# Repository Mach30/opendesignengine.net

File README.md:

This is a static checkout of opendesignengine.net, a web portal that was developed by [Mach 30](http://mach30.org) to make it so that open source hardware projects could post not just the plans, but the entire design process of their hardware projects.

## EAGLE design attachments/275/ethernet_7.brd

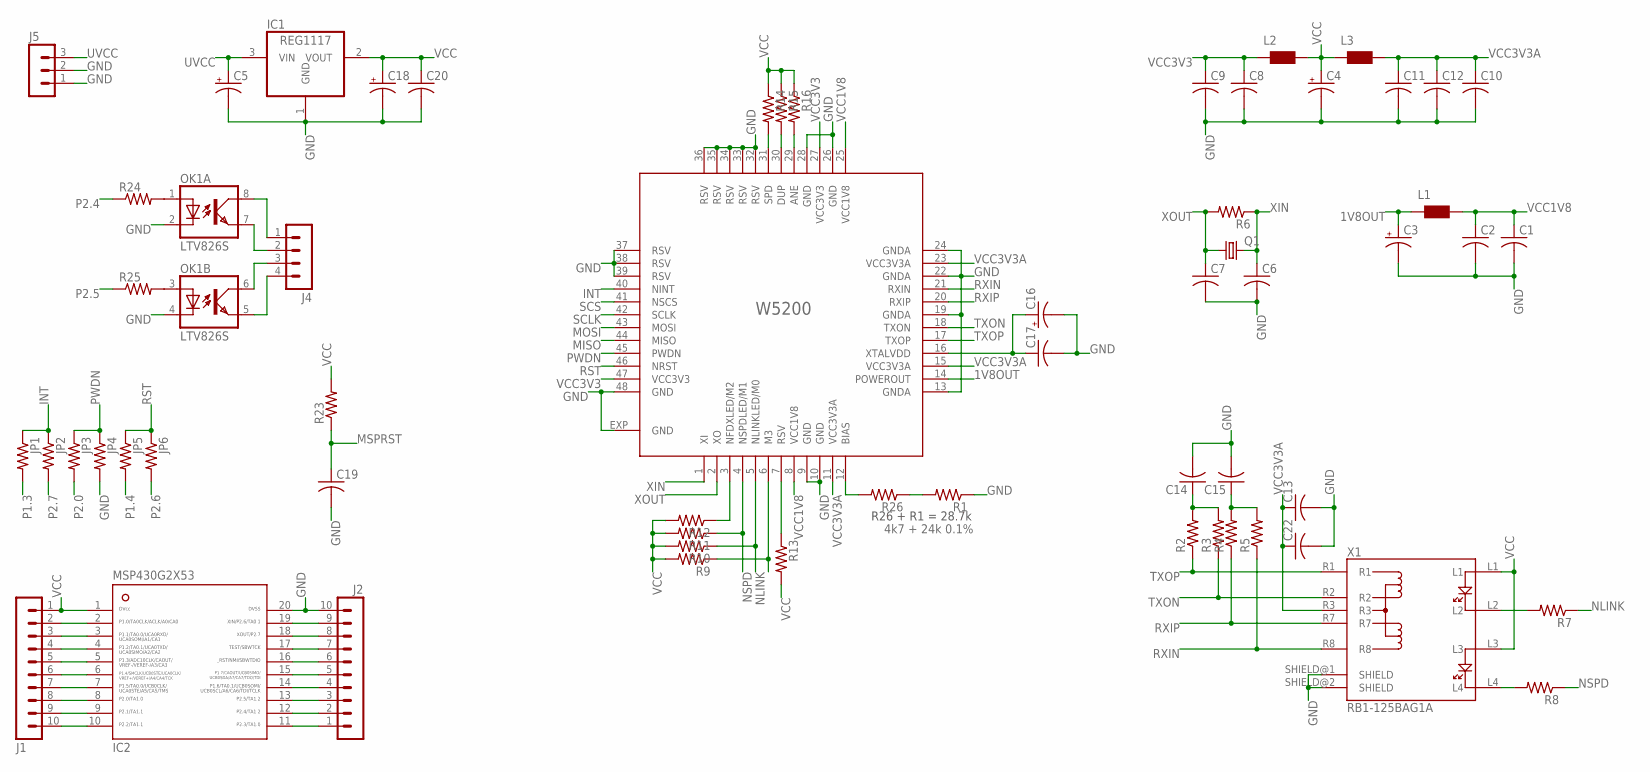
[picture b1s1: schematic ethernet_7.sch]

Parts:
C1, C2, C6, C7, C8, C9, C10, C11, C12, C13, C14, C15, C17, C19, C20, C22: C-USC0603; C0603
C3, C4, C16: CPOL-USA/3216-18R; A/3216-18R
C5, C18: CPOL-USB/3528-21R; B/3528-21R
IC1: REG1117; SOT223
IC2: MSP430G2X53-20N20; N20
J1, J2: MA10-1NOTXT; MA10-1-NOTXT
J4: MA04-1-ALLV; MA04-1
J5: MA03-1
JP1, JP2, JP3, JP4, JP5, JP6: R-US_R0603; R0603
L1, L2, L3: WE-CBF_0603; 0603
OK1: LTV826S; DIL8-SMD
Q1: CRYSTALSM49; SM49
R1, R2, R3, R4, R5, R6, R7, R8, R9, R10, R11, R12, R13, R14, R15, R16, R23, R24, R25, R26: R-US_R0603; R0603
W5200: W52003; QFN48-3
X1: RB1-125BAG1A

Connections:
1V8OUT: C3.+, L1.1, W5200.14 (POWEROUT)
BIAS: R26.2, W5200.12 (BIAS)
GND: C1.2, C2.2, C3.-, C4.-, C5.-, C6.2, C7.2, C8.2, C9.2, C10.2, C11.2, C12.2, C13.2, C14.2, C15.2, C16.-, C17.2, C18.-, C19.2, C20.2, C22.2, IC1.1 (GND), IC2.20, J2.10, J5.1, J5.2, JP4.2, OK1.2 (C), OK1.4 (C), R1.1, W5200.9 (GND), W5200.10 (GND), W5200.13 (GNDA), W5200.19 (GNDA), W5200.22 (GNDA), W5200.24 (GNDA), W5200.26 (GND), W5200.28 (GND), W5200.32 (RSV), W5200.33 (RSV), W5200.34 (RSV), W5200.35 (RSV), W5200.36 (RSV), W5200.37 (RSV), W5200.38 (RSV), W5200.39 (RSV), W5200.48 (GND), W5200.EXP (GND), X1.SHIELD@1 (SHIELD), X1.SHIELD@2 (SHIELD)
INT: JP1.1, JP2.1, W5200.40 (NINT)
M2: R12.1, W5200.3 (NFDXLED/M2)
M3: R9.1, W5200.6 (M3)
MISO: IC2.14, J2.4, W5200.44 (MISO)
MOSI: IC2.15, J2.5, W5200.43 (MOSI)
MSPRST: C19.1, IC2.16, J2.6, R23.1
unnamed: J4.2, OK1.7 (EMIT)
unnamed: J4.1, OK1.8 (COL)
unnamed: IC2.3, J1.3
unnamed: IC2.4, J1.4
unnamed: J4.3, OK1.6 (COL)
unnamed: J4.4, OK1.5 (EMIT)
unnamed: OK1.1 (A), R24.2
unnamed: OK1.3 (A), R25.2
unnamed: R1.2, R26.1
unnamed: IC2.17, J2.7
unnamed: IC2.9, J1.9
unnamed: IC2.10, J1.10
unnamed: IC2.11, J2.1
unnamed: R7.2, X1.L2
unnamed: R8.2, X1.L4
unnamed: R14.2, W5200.31 (SPD)
unnamed: R15.2, W5200.30 (DUP)
unnamed: C14.1, R2.2, R3.2
unnamed: C15.1, R4.2, R5.2
unnamed: R16.2, W5200.29 (ANE)
NLINK: R7.1, R10.1, W5200.5 (NLINKLED/M0)
NSPD: R8.1, R11.1, W5200.4 (NSPDLED/M1)
P1.3: IC2.5, J1.5, JP1.2
P1.4: IC2.6, J1.6, JP5.2
P2.0: IC2.8, J1.8, JP3.2
P2.4: IC2.12, J2.2, R24.1
P2.5: IC2.13, J2.3, R25.1
P2.6: IC2.19, J2.9, JP6.2
P2.7: IC2.18, J2.8, JP2.2
PWDN: JP3.1, JP4.1, W5200.45 (PWDN)
RST: JP5.1, JP6.1, W5200.46 (NRST)
RSV: R13.1, W5200.7 (RSV)
RXIN: R5.1, W5200.21 (RXIN), X1.R8
RXIP: R4.1, W5200.20 (RXIP), X1.R7
SCLK: IC2.7, J1.7, W5200.42 (SCLK)
SCS: IC2.2, J1.2, W5200.41 (NSCS)
TXON: R3.1, W5200.18 (TXON), X1.R2
TXOP: R2.1, W5200.17 (TXOP), X1.R1
UVCC: C5.+, IC1.3 (VIN), J5.3
VCC: C4.+, C18.+, C20.1, IC1.2 (VOUT), IC2.1, J1.1, L2.2, L3.1, R9.2, R10.2, R11.2, R12.2, R13.2, R14.1, R15.1, R16.1, R23.2, X1.L1, X1.L3
VCC1V8: C1.1, C2.1, L1.2, W5200.8 (VCC1V8), W5200.25 (VCC1V8)
VCC3V3: C8.1, C9.1, L2.1, W5200.27 (VCC3V3), W5200.47 (VCC3V3)
VCC3V3A: C10.1, C11.1, C12.1, C13.1, C22.1, L3.2, W5200.11 (VCC3V3A), W5200.15 (VCC3V3A), W5200.23 (VCC3V3A), X1.R3
XIN: C6.1, Q1.2, R6.1, W5200.1 (XI)
XOUT: C7.1, Q1.1, R6.2, W5200.2 (XO)
XTALVDD: C16.+, C17.1, W5200.16 (XTALVDD)

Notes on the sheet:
R26 + R1 = 28.7k
4k7 + 24k 0.1%

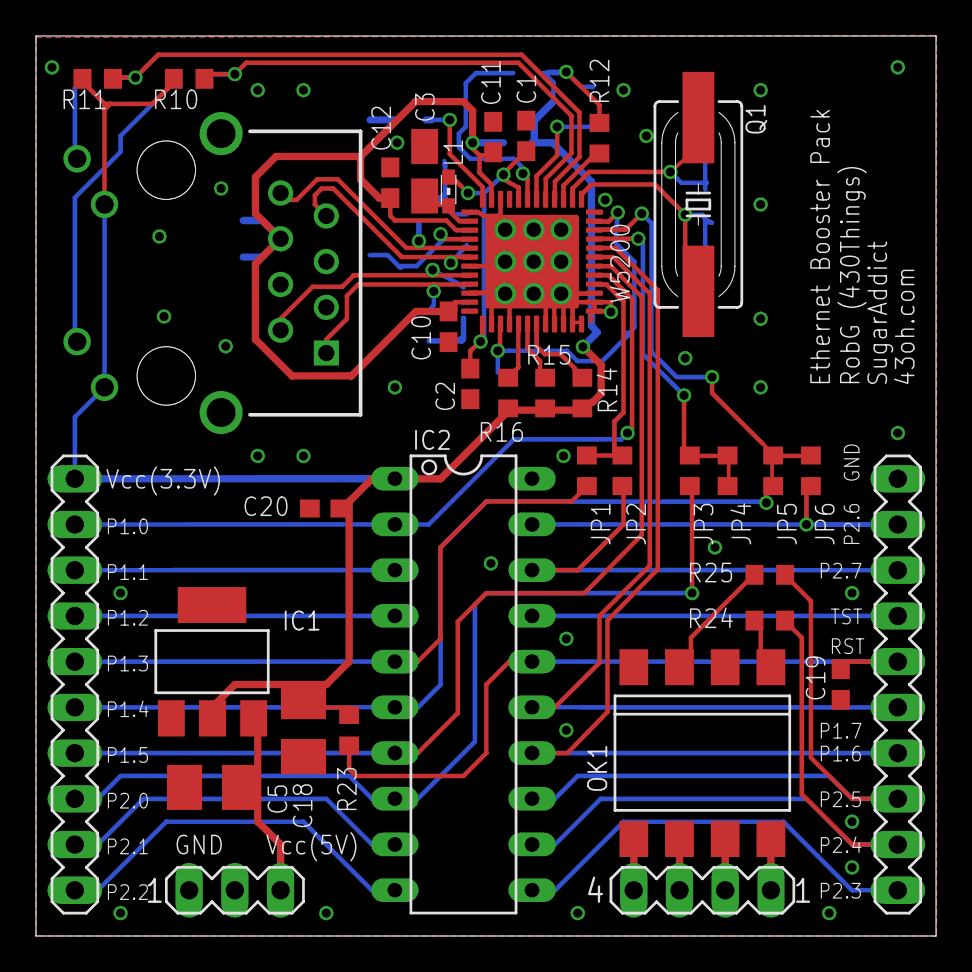
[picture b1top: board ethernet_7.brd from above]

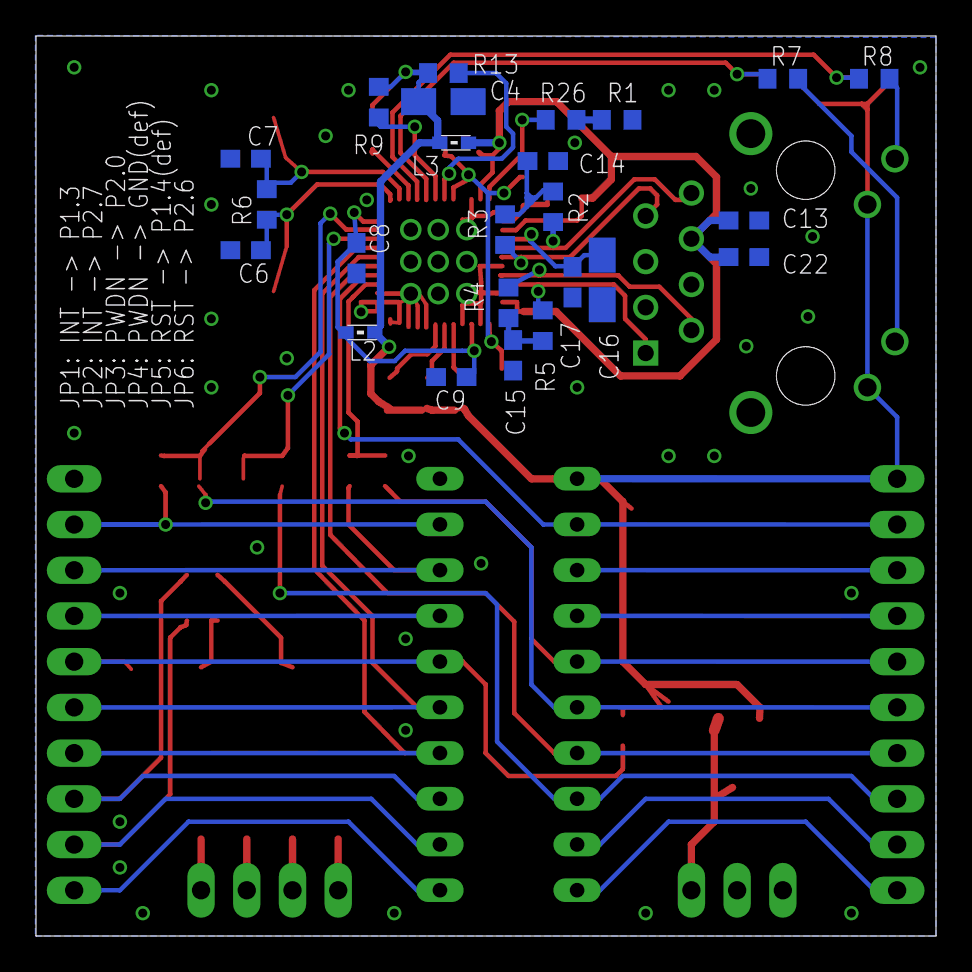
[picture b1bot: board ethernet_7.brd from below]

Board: 2 copper layers, 50.0 x 50.0 mm, 60 parts (24 on the bottom side), 55 nets.

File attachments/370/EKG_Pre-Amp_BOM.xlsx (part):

REFDES | Quantity | Value | Tolerance | Function | MFG | MFG P/N | Part Description | Package | Datasheet Link | Vendor | Vendor P/N | Comments
Connectors | CONNECTORS
P1, P2 | 2 | '--- | '--- | Battery Connection - Screw Terminal | TE Connectivity / AMP | 282834-2 | Fixed Terminal Blocks 2P SIDE ENTRY 2.54mm | TH - 2.54mm pitch | http://www.te.com/catalog/pn/en/282834-2?RQPN=282834-2 | Mouser | 571-282834-2 | This part is generic.
P3, P4 | 2 | DNI | '--- | Alternate Input Connection Block - Screw Terminal | TE Connectivity / AMP | 282834-3 | Fixed Terminal Blocks 3P SIDE ENTRY 2.54mm | TH - 2.54mm pitch | http://www.te.com/catalog/pn/en/282834-3?RQPN=282834-3 | Mouser | 571-2828343 | This part is generic.
BP1 | 1 | YELLOW | '--- | Input Connector - Binding Post | Johnson / Emerson Connectivity Solutions | 111-0107-001 | Test Plugs & Test Jacks BINDING POST YELLOW | Panel Mount - Solder or Screw | http://emersonconnectivity.com/OA_HTML/ibeCCtpItmDspRte.jsp?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 | Mouser | 530-111-0107-1 | This part is generic.
BP2 | 1 | WHITE | '--- | Input Connector - Binding Post | Johnson / Emerson Connectivity Solutions | 111-0101-001 | Test Plugs & Test Jacks BINDING POST WHITE | Panel Mount - Solder or Screw | http://emersonconnectivity.com/OA_HTML/ibeCCtpItmDspRte.jsp?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 | Mouser | 530-111-0101-1 | This part is generic.
BP3 | 1 | BLACK | '--- | Input Connector - Binding Post | Johnson / Emerson Connectivity Solutions | 111-0103-001 | Test Plugs & Test Jacks BINDING POST BLACK | Panel Mount - Solder or Screw | http://emersonconnectivity.com/OA_HTML/ibeCCtpItmDspRte.jsp?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 | Mouser | 530-111-0103-1 | This part is generic.
BP4, BP5, BP6 | 3 | RED | '--- | Input Connector - Binding Post | Johnson / Emerson Connectivity Solutions | 111-0102-001 | Test Plugs & Test Jacks BINDING POST RED | Panel Mount - Solder or Screw | http://emersonconnectivity.com/OA_HTML/ibeCCtpItmDspRte.jsp?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 | Mouser | 530-111-0102-1 | This part is generic.
BNC1, BNC2, BNC3, BNC4 | 4 | '--- | '--- | Output Connector - BNC | TE Connectivity / AMP | 5227161-6 | RT/A BNC 50 Ohms, PCB-Mount | Through-Hole with Panel-Mount Face, Right-Angle Launch | http://www.te.com/catalog/pn/en/5227161-6?RQPN=5227161-6 | Mouser | 571-5227161-6 | This part is generic.
Resistors/Jumpers | RESISTORS/JUMPERS
G1, G3, G4, G5 | 4 | 11k | '1% | Gain Resistor for U1, U3, U4, U5 (respectively) | Yageo | MFR-25FBF52-11K | RES 11K OHM 1/4W 1% AXIAL | TH | http://www.yageo.com/documents/recent/General%20Type_MFR.pdf | Digikey | 11.0KXBK-ND | This part needs 1% tolerance.
R1 | 1 | 2M | '1% | Single-Pole HPF - goes between differential amplifier gain stages | Stackpole Electronics Inc. | RNF14FTD2M00 | RES 2M OHM 1/4W 1% AXIAL | TH | http://www.seielect.com/Catalog/SEI-RNF_RNMF.pdf | Digikey | RNF14FTD2M00CT-ND | This part is generic (it doesn't really need 1% tolerance).
R2 | 1 | 2.1k | '1% | Gain Resistor for U2 | Yageo | MFR-25FBF52-2K1 | RES 2.1K OHM 1/4W 1% AXIAL | TH | http://www.yageo.com/documents/recent/General%20Type_MFR.pdf | Digikey | 2.10KXBK-ND | This part needs 1% tolerance.
R3, R4, R5, R6, R7, R8 | 6 | 43k | '5% | Offset Adjust leg resistors | Panasonic Electronic Components | ERD-S2TJ433V | RES 43K OHM 1/4W 5% AXIAL | TH | http://industrial.panasonic.com/www-data/pdf/AOA0000/AOA0000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 | Digikey | P43KBACT-ND | PART IS OBSOLETE! Needs replacement identified.
R9, R10 | 2 | '300 | '5% | Indicator LED limit resistors | Stackpole Electronics Inc. | CF14JT300R | RES 300 OHM 1/4W 5% CARBON FILM | TH | http://www.seielect.com/catalog/SEI-CF_CFM.pdf | Digikey | CF14JT300RCT-ND | This part is generic (size it to match how bright you want the indicator LEDs t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
R11 | 0 | DNI | '--- | this is a bug/error (with C2) | '--- | '--- | '--- | '--- | '--- | '--- | '---
R12, R13, R14 | 0 | DNI | '--- | Jumpers (0 Ohm) - Connects P3 pins to BP1, BP2 and BP3 (respectively) | '--- | '--- | '--- | '--- | '--- | '--- | '--- | This part is generic.
Capacitors | CAPACITORS
C1, C20, C22 | 3 | 1uF | '10% | C1 = Single-Pole HPF - goes between differential amplifier gain stages. C20, C2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 | TDK Corporation | FK28X5R1A105K | CAP CER 1UF 10V 10% RADIAL | TH, RADIAL | http://product.tdk.com/capacitor/leadmlcc/en/documents/leadm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 | Digikey | 445-2851-ND | This part is generic.
C2 | 0 | DNI | '--- | this is a bug/error (with R11) | '--- | '--- | '--- | '--- | '--- | '--- | '---
C3, C5, C7, C9, C11, C14, C15, C18, C19 | 9 | 0.47uF | '10% | Decoupling Capacitor (two per IC) | Vishay BC Components | K474K20X7RF5UH5 | CAP CER 0.47UF 50V 10% RADIAL | TH, RADIAL | http://www.vishay.com/docs/45171/kseries.pdf | Digikey | BC2689CT-ND | This part is generic.
C4, C6, C8, C10, C12, C13, C16, C17, C21 | 9 | 0.1uF | '10% | Decoupling Capacitor (two per IC) | Vishay BC Components | K104K15X7RF5TL2 | CAP CER 0.1UF 50V 10% RADIAL | TH, RADIAL | http://www.vishay.com/docs/45171/kseries.pdf | Digikey | BC1084CT-ND | This part is generic.
Potentiometers | POTENTIOMETERS
POT1, POT2, POT3 | 3 | 10k | '20% | Offset Adjust Knob for Single-Ended Amplifiers | Panasonic Electronic Components | EVU-F2AF30B14 | POT 10K OHM 9MM VERT NO BUSHING | TH | http://www.panasonic.com/industrial/components/pdf/aok0000ce4.pdf | Digikey | P3C3103-ND | This part was selected for its value (10k), it's linearity, its shaft type, and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
Switches | SWITCHES
S2 | 1 | SPDT, 0.4VA, 28V | '--- | Power Toggle Switch | NKK Switches | M2012SS1G03 | SWITCH TOGGLE SPDT 0.4VA 28V | TH, Panel-Mount | http://www.nkkswitches.com/pdf/MtogglesBushing.pdf | Digikey | 360-1800-ND | This part is fairly generic. It was picked because it's got a nice clicking act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
Active Components | ACTIVE COMPONENTS
Q1, Q2 | 2 | --- | '--- | Power Supply N-Fet - Connects Batteries to respective power supply rails when S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 | Alpha & Omega Semiconductor Inc | AOD4102 | MOSFET N-CH 30V 19A TO-252 | SMT, TO-252 | http://www.aosmd.com/res/data_sheets/AOD4102.pdf | Digikey | 785-1104-1-ND | PART IS OBSOLETE! Needs replacement identified.
U1, U3, U4, U5 | 4 | G = 10 | '--- | Instrumentation Amplifier - Gain = 10 | Analog Devices | AD623ANZ | IC AMP INST R-R LP 8DIP | 8-DIP | http://www.analog.com/static/imported-files/data_sheets/AD623.pdf | Digikey | AD623ANZ-ND | This part was specifically picked for its performance.
U2 | 1 | G = 100 | '--- | Instrumentation Amplifier - Gain = 100 | Analog Devices | AD627ANZ | IC AMP INST R-R 25MA 8DIP | 8-DIP | http://www.analog.com/static/imported-files/data_sheets/AD627.pdf | Digikey | AD627ANZ-ND | This part was specifically picked for its performance.
LEDs/Diodes | LEDS/DIODES
VEE_LED, VCC_LED | 2 | RED | '--- | Power Supply Indicator LEDs | Everlight Electronics Co. Ltd. | MV8112 | LED SS ALGAAS SUP RED CLEAR 5MM | TH, RADIAL | http://media.digikey.com/PDF/Data%20Sheets/Everlight%20PDFs/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 | Digikey | 1080-1134-ND | This part is generic (pick any same-sized LED you like, as long as Vf < 2.5V).
Other Parts | OTHER ELECTRICAL/MECHANICAL ASSEMBLY PARTS (NOT IN CIRCUIT, SO NOT NOTED ON SCH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
Enclosure | 1 | '--- | '--- | Holds it all together | LBM Heager | KAB3432-BLK | Die Cast Enclosure Semi-Gloss BLACK | 4-11/16"L x 3-11/16"W x 2-7/32"H | http://www.minute-man.com/acatalog/LMB_Heeger_Die_Cast_Enclo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 | Minute Man Electronics | LMB Heeger KAB-3432BLK | This part requires hand-modifications to the lid and body in order to accommoda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
Potentiometer Knobs | 3 | '--- | '--- | Knobs fit over potentiometer slotted-D shaft. Act as indicator, make it easier 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 | Eagle Plastic Devices | 450-4760 | Knobs & Dials SOFT TOUCH D SHAFT | '--- | http://www.mouser.com/ds/2/209/EPD-200220-198922.pdf | Mouser | 450-4760 | This part is generic.
Battery Holders | 2 | 2xAA | '--- | The batteries! One battery pack provides the +3V supply (via P1), the other pro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 | Eagle Plastic Devices | 12BH325/C-GR | Battery Holders, Snaps & Contacts 2XAA 6" LDS COVER | --- | http://www.mouser.com/ds/2/209/EPD-200416-191665.pdf | Mouser | 12BH325/C-GR | This part is pretty generic - the important feature here is that it have a lid 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

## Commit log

2023-03-20 Initial scrape
